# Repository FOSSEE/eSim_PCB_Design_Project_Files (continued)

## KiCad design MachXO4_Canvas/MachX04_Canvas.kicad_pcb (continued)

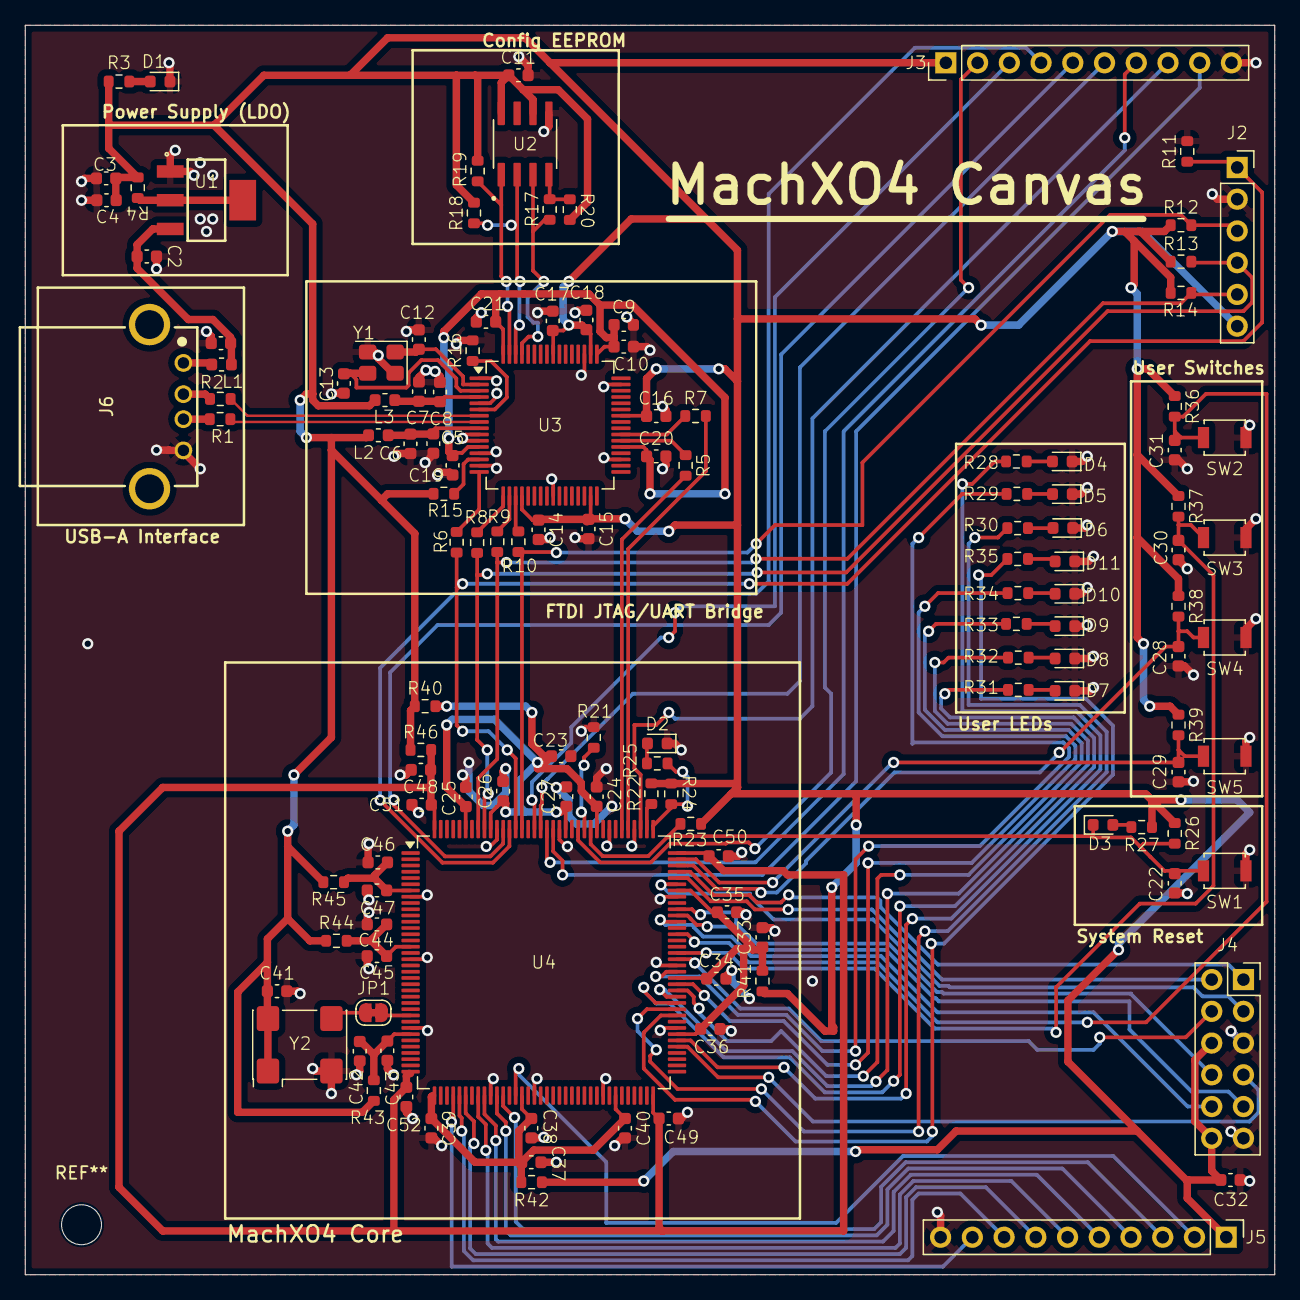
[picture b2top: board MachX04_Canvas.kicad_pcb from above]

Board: 2 copper layers, 100.0 x 100.0 mm, 129 parts (0 on the bottom side), 92 nets.

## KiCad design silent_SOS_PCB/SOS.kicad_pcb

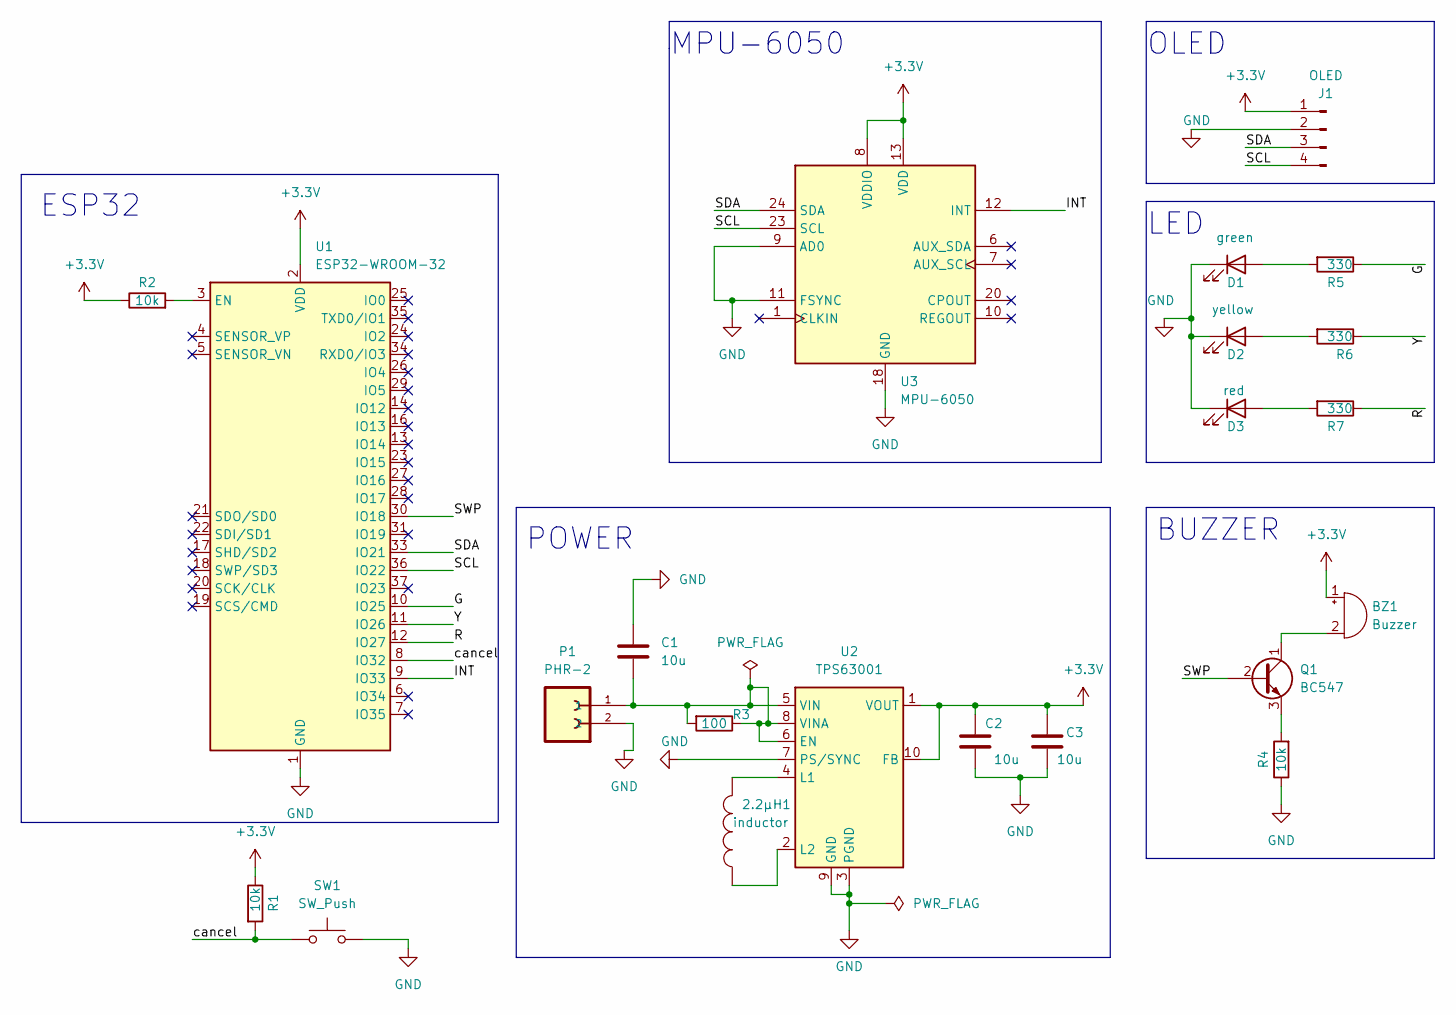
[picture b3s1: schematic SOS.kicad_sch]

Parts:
2.2µH1: inductor; L_0805_2012Metric
BZ1: Buzzer; Buzzer_CUI_CPT-9019S-SMT
C1, C2, C3: 10u; C_0805_2012Metric
D1: green; LED_0805_2012Metric
D2: yellow; LED_0805_2012Metric
D3: red; LED_0805_2012Metric
J1: OLED; PinHeader_1x04_P2.54mm_Vertical
P1: PHR-2; JST_PH_B2B-PH-K_1x02_P2.00mm_Vertical; MPN PHR-2
Q1: BC547; TO-92_Inline
R1, R2, R4: 10k; R_0805_2012Metric
R3: 100; R_0805_2012Metric
R5, R6, R7: 330; R_0805_2012Metric
SW1: SW_Push; SW_Push_SPST_NO_Alps_SKRK
U1: ESP32-WROOM-32
U2: TPS63001; Texas_DRC0010J_ThermalVias
U3: MPU-6050; InvenSense_QFN-24_4x4mm_P0.5mm

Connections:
+3.3V: BZ1.1 (-), C2.1, C3.1, J1.1, R1.1, R2.1, U1.2 (VDD), U2.1 (VOUT), U2.10 (FB), U3.8 (VDDIO), U3.13 (VDD)
/G: R5.1, U1.10 (IO25)
/INT: U1.9 (IO33), U3.12 (INT)
/R: R7.1, U1.12 (IO27)
/SCL: J1.4, U1.36 (IO22), U3.23 (SCL)
/SDA: J1.3, U1.33 (IO21), U3.24 (SDA)
/SWP: Q1.2 (B), U1.30 (IO18)
/Y: R6.1, U1.11 (IO26)
/cancel: R1.2, SW1.1, U1.8 (IO32)
GND: C1.1, C2.2, C3.2, D1.1 (K), D2.1 (K), D3.1 (K), J1.2, P1.2, R4.1, SW1.2, U1.1 (GND), U1.15 (GND), U1.38 (GND), U1.39 (GND), U2.3 (PGND), U2.7 (PS/SYNC), U2.9 (GND), U2.11 (PGND), U3.9 (AD0), U3.11 (FSYNC), U3.18 (GND)
unnamed: 2.2µH1.1, U2.2 (L2)
unnamed: 2.2µH1.2, U2.4 (L1)
unnamed: BZ1.2 (+), Q1.1 (C)
unnamed: C1.2, P1.1, R3.1, R3.2, U2.5 (VIN), U2.6 (EN), U2.8 (VINA)
unnamed: D1.2 (A), R5.2
unnamed: D2.2 (A), R6.2
unnamed: D3.2 (A), R7.2
unnamed: Q1.3 (E), R4.2
unnamed: R2.2, U1.3 (EN)

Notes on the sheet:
LED
POWER
BUZZER
ESP32
OLED
MPU-6050

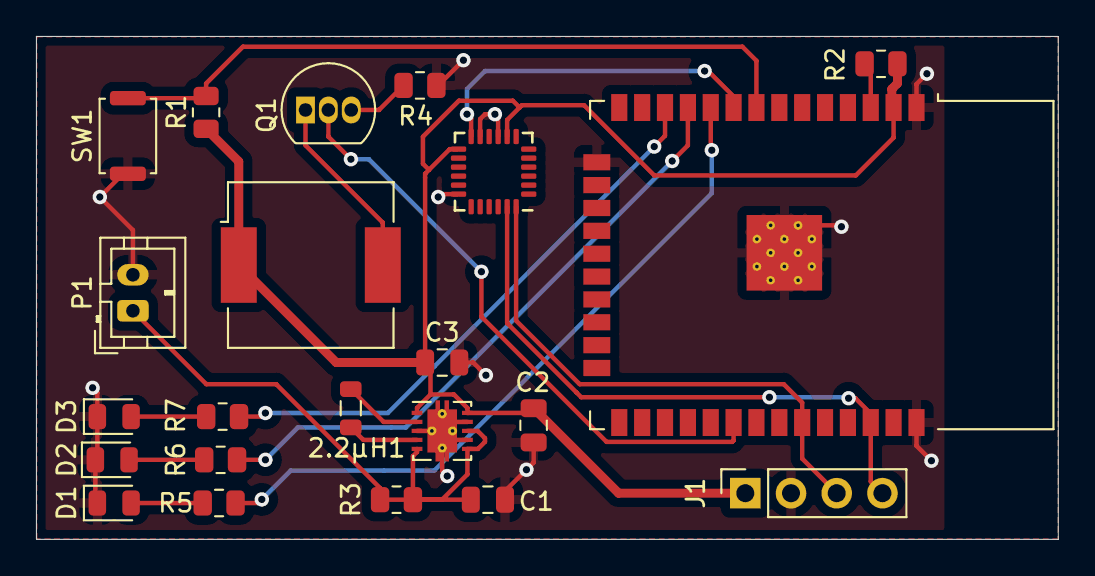
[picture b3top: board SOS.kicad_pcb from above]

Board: 2 copper layers, 56.8 x 27.9 mm, 22 parts (0 on the bottom side), 19 nets.

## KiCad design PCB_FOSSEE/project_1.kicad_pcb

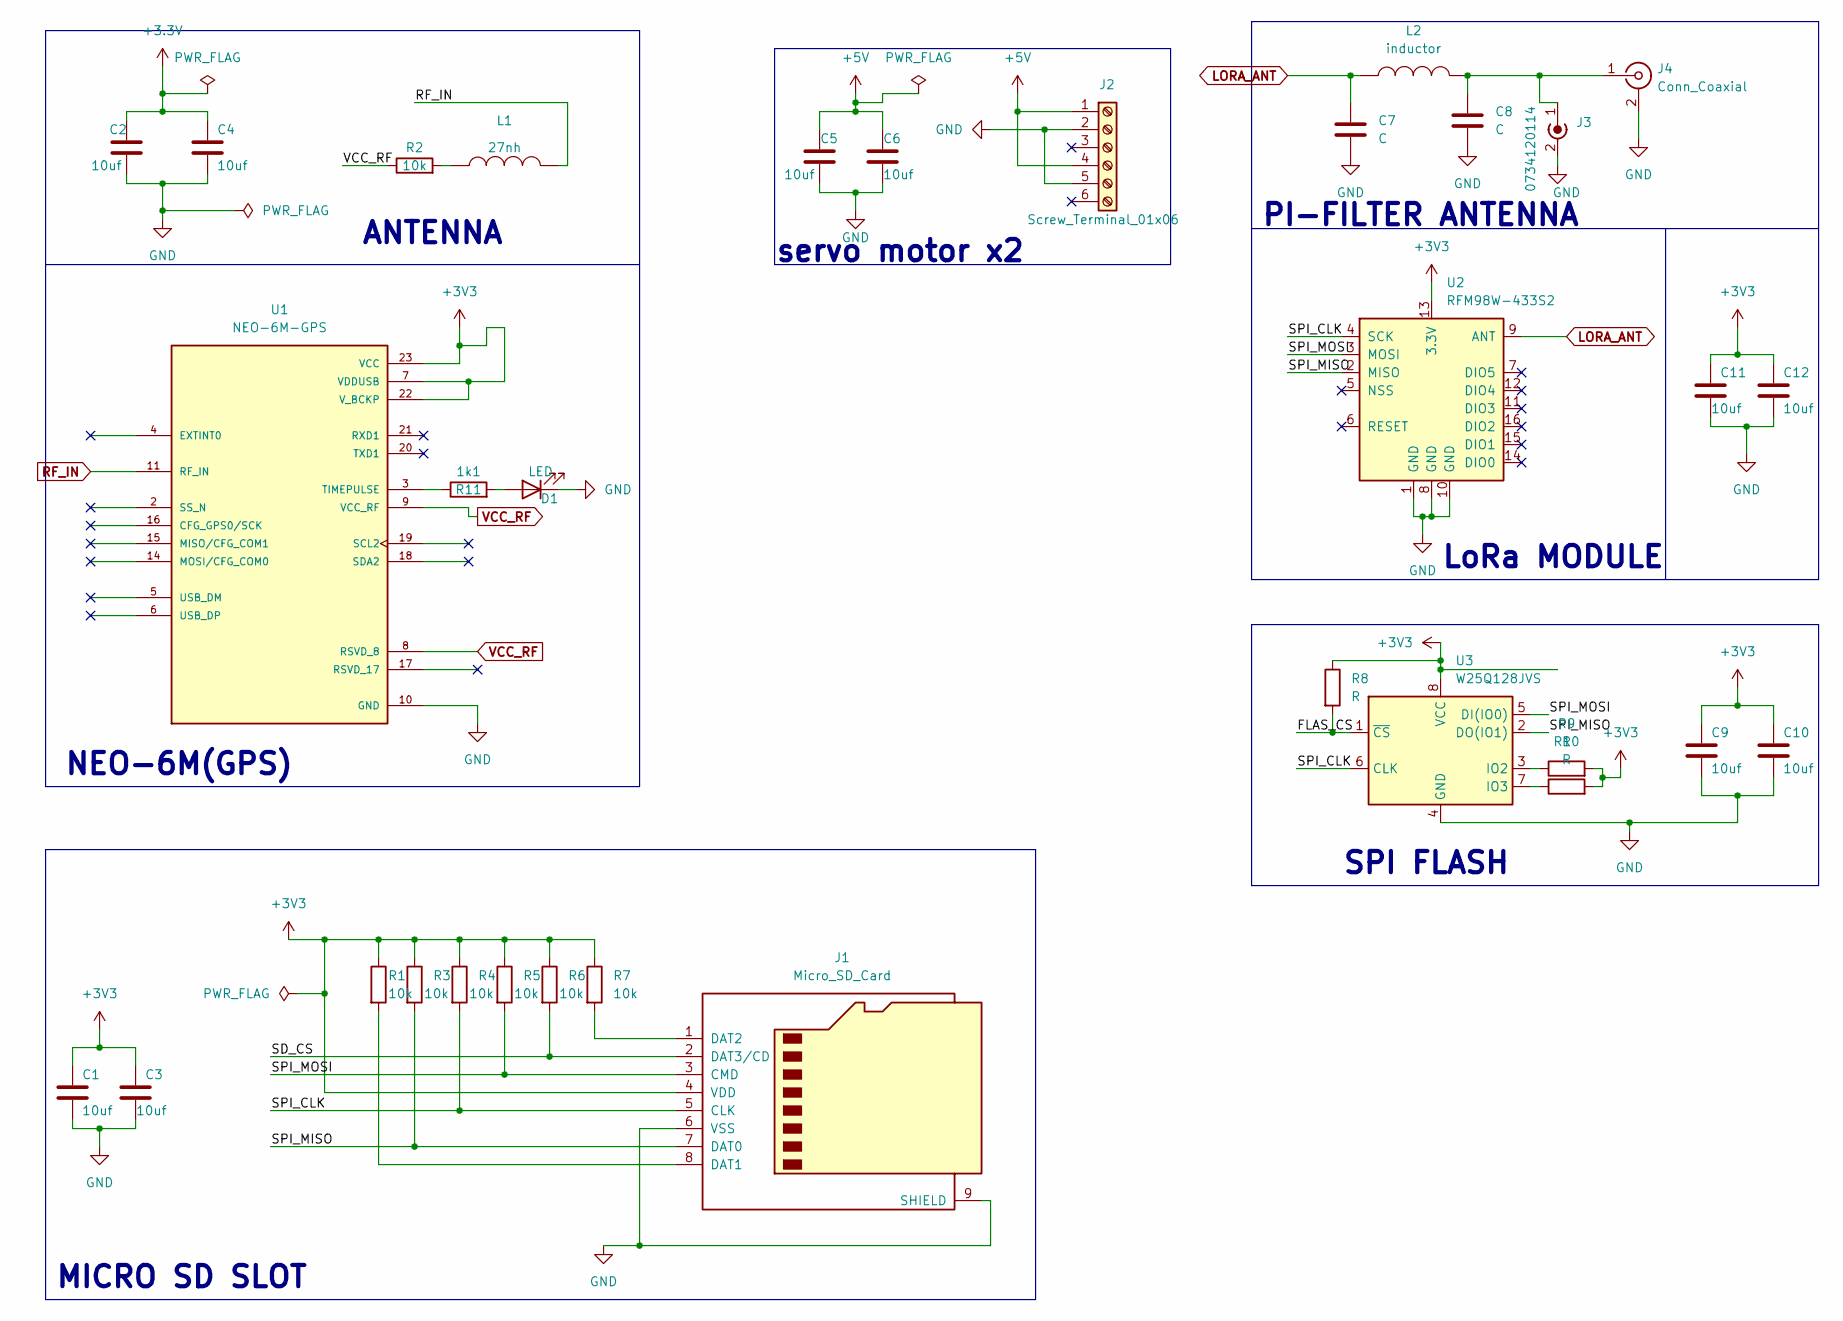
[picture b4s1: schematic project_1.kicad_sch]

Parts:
C1, C2, C3, C4, C5, C6, C9, C10, C11, C12: 10uf; C_0805_2012Metric
C7, C8: C; C_0805_2012Metric
D1: LED; LED_0805_2012Metric
J1: Micro_SD_Card; microSD_HC_Wuerth_693072010801
J2: Screw_Terminal_01x06; TerminalBlock_bornier-6_P5.08mm
J3: 0734120114; SMA_Molex_73251-1153_EdgeMount_Horizontal
J4: Conn_Coaxial; SMA_Molex_73251-2120_EdgeMount_Horizontal
L1: 27nh; L_0805_2012Metric
L2: inductor; L_0805_2012Metric
R1, R2, R3, R4, R5, R6, R7: 10k; R_0805_2012Metric
R8, R9, R10: R; R_0805_2012Metric
R11: 1k1; R_0805_2012Metric
U1: NEO-6M-GPS; ublox_NEO; MPN NEO-6M-GPS
U2: RFM98W-433S2; HOPERF_RFM9XW_SMD
U3: W25Q128JVS; SOIC-8_5.23x5.23mm_P1.27mm

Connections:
+3.3V: C2.1, C4.1
+3V3: C1.1, C3.1, C9.1, C10.1, C11.1, C12.1, J1.4 (VDD), R1.1, R3.1, R4.1, R5.1, R6.1, R7.1, R8.1, R9.2, R10.2, U1.7 (VDDUSB), U1.22 (V_BCKP), U1.23 (VCC), U2.13 (3.3V), U3.8 (VCC)
+5V: C5.1, C6.1, J2.1, J2.4
/FLAS_CS: R8.2, U3.1 (~CS)
/SD_CS: J1.2 (DAT3/CD), R6.2
/SPI_CLK: J1.5 (CLK), R4.2, U2.4 (SCK), U3.6 (CLK)
/SPI_MISO: J1.7 (DAT0), R3.2, U2.2 (MISO), U3.2 (DO(IO1))
/SPI_MOSI: J1.3 (CMD), R5.2, U2.3 (MOSI), U3.5 (DI(IO0))
GND: C1.2, C2.2, C3.2, C4.2, C5.2, C6.2, C7.2, C8.2, C9.2, C10.2, C11.2, C12.2, D1.1 (K), J1.6 (VSS), J1.9 (SHIELD), J2.2, J2.5, J3.2 (Ext), J4.2 (Ext), U1.10 (GND), U1.12 (GND), U1.13 (GND), U1.24 (GND), U2.1 (GND), U2.8 (GND), U2.10 (GND), U3.4 (GND)
LORA_ANT: C7.1, L2.1, U2.9 (ANT)
unnamed 10: R11.1, U1.3 (TIMEPULSE); also elsewhere on the board
unnamed 11: D1.2 (A), R11.2; also elsewhere on the board
unnamed: C8.1, J3.1 (In), J4.1 (In), L2.2
unnamed: J1.1 (DAT2), R7.2
unnamed: J1.8 (DAT1), R1.2
unnamed: L1.1, R2.2
unnamed: R9.1, U3.3 (IO2)
unnamed: R10.1, U3.7 (IO3)
RF_IN: L1.2, U1.11 (RF_IN)
VCC_RF: R2.1, U1.8 (RSVD_8), U1.9 (VCC_RF)

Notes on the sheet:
MICRO SD SLOT
SPI FLASH
ANTENNA
servo motor x2
LoRa MODULE
NEO-6M(GPS)
PI-FILTER ANTENNA

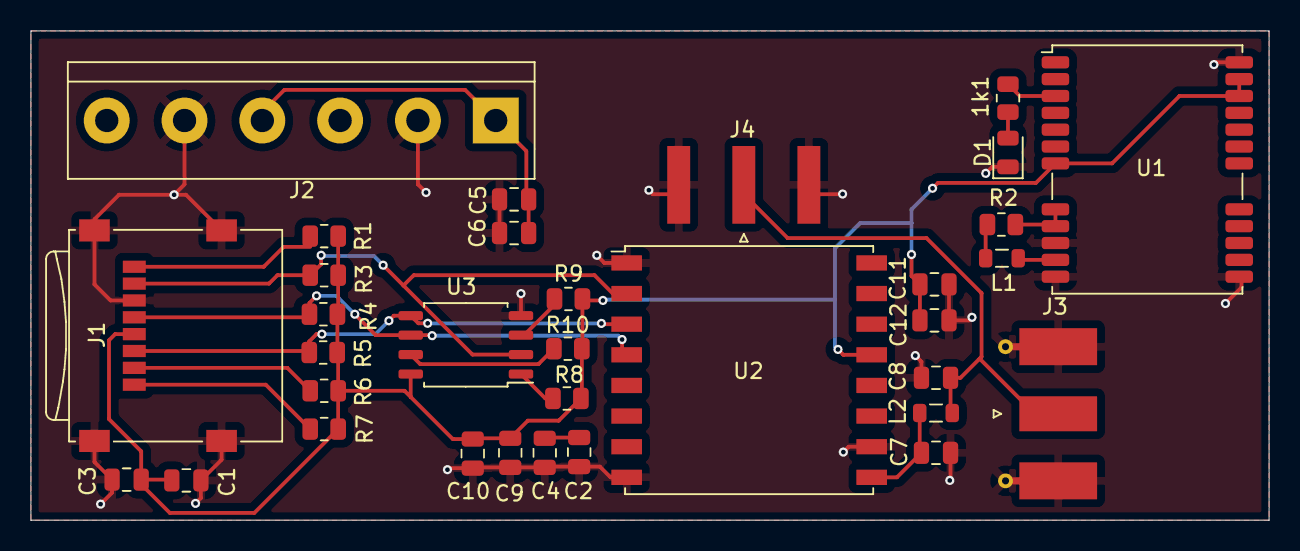
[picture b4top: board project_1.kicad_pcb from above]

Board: 2 copper layers, 80.8 x 32.0 mm, 33 parts (0 on the bottom side), 20 nets.

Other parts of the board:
1k1: R; R_0805_2012Metric

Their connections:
unnamed 10: 1k1.1; also elsewhere on the board
unnamed 11: 1k1.2; also elsewhere on the board

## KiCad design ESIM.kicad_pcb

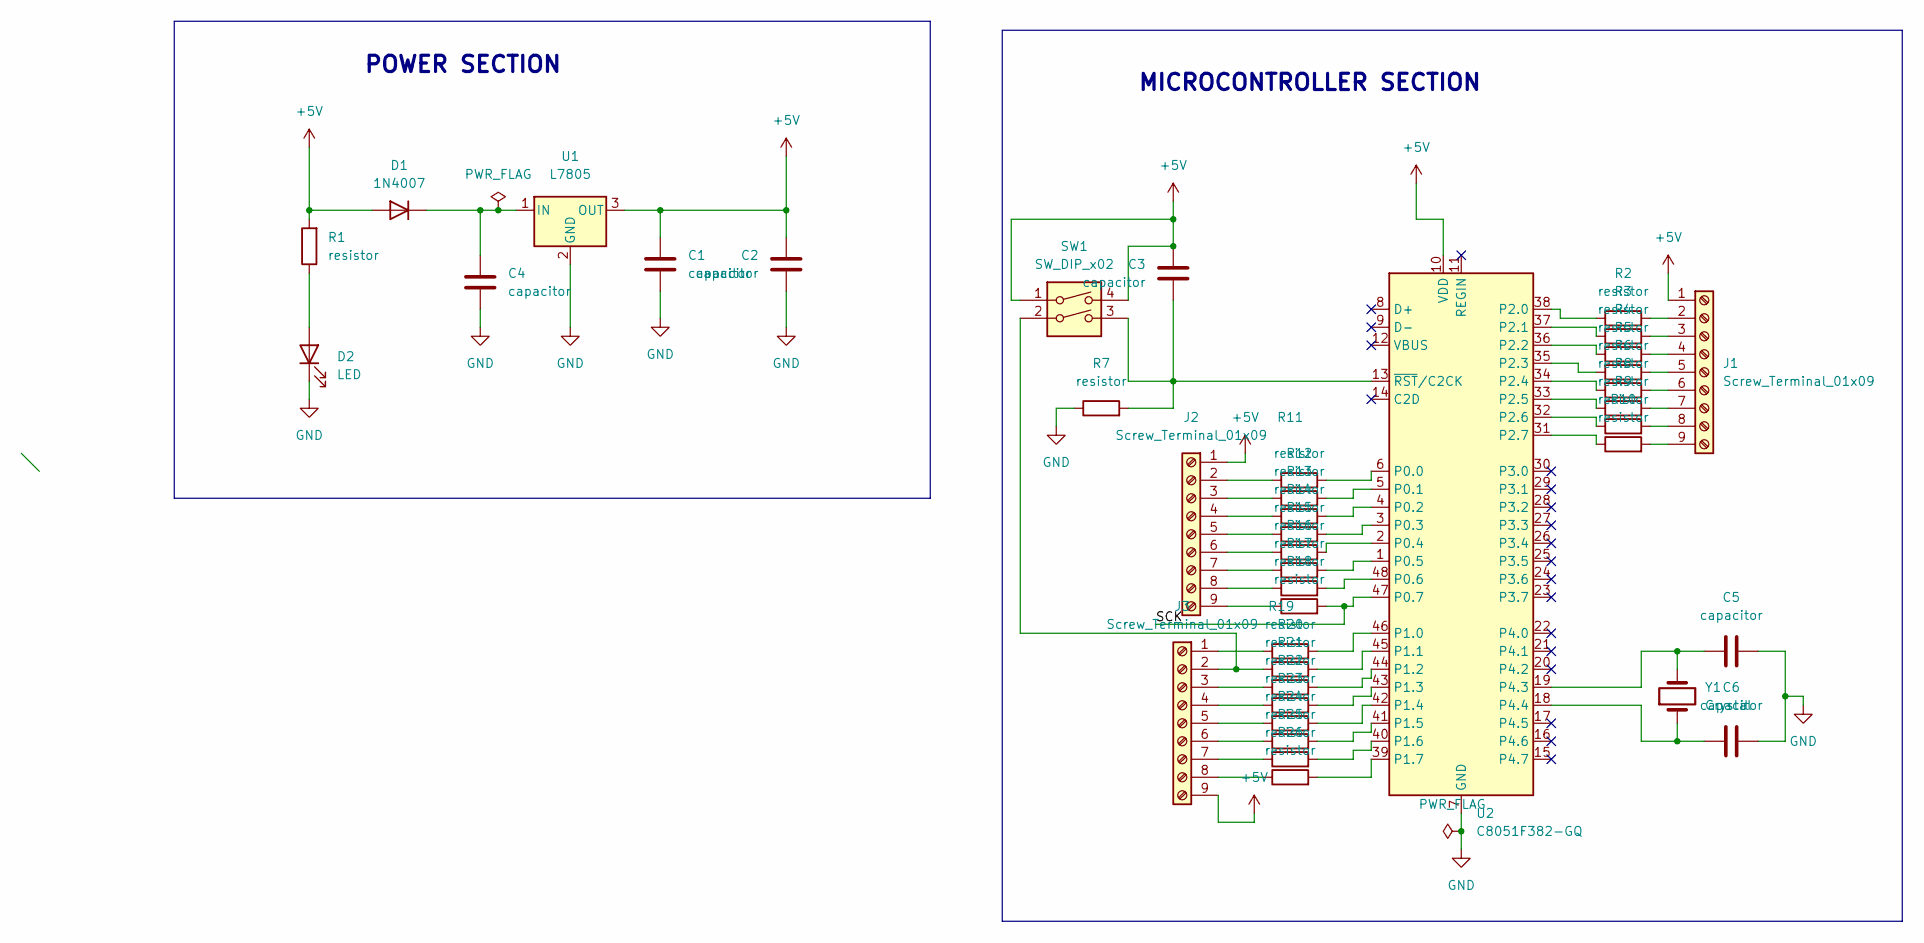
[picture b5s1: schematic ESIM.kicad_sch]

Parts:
C1, C2, C3, C4, C5, C6: capacitor; C_0603_1608Metric_Pad1.08x0.95mm_HandSolder
D1: 1N4007; D_DO-41_SOD81_P10.16mm_Horizontal
D2: LED; LED_0201_0603Metric
J1, J2, J3: Screw_Terminal_01x09; PinHeader_1x09_P1.00mm_Horizontal
R1, R2, R3, R4, R5, R6, R7, R8, R9, R10, R11, R12, R13, R14, R15, R16, R17, R18, R19, R20, R21, R22, R23, R24, R25, R26: resistor; R_0201_0603Metric
SW1: SW_DIP_x02; SW_DIP_SPSTx02_Slide_6.7x6.64mm_W6.73mm_P2.54mm_LowProfile_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
U1: L7805; TO-220-3_Vertical
U2: C8051F382-GQ; TQFP-48_7x7mm_P0.5mm
Y1: Crystal; Crystal_AT310_D3.0mm_L10.0mm_Horizontal

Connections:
+5V: C1.2, C2.2, C3.2, D1.2 (A), J1.1, J2.1, J3.9, R1.2, SW1.1, SW1.4, U1.3 (OUT), U2.10 (VDD)
/SCK: R18.2, U2.47 (P0.7)
GND: C1.1, C2.1, C4.1, C5.1, C6.1, D2.1 (K), R7.1, U1.2 (GND), U2.7 (GND)
unnamed: C3.1, R7.2, SW1.3, U2.13 (~RST/C2CK)
unnamed: C4.2, D1.1 (K), U1.1 (IN)
unnamed: C5.2, U2.19 (P4.3), Y1.2
unnamed: C6.2, U2.18 (P4.4), Y1.1
unnamed: D2.2 (A), R1.1
unnamed: J1.2, R2.2
unnamed: J1.3, R3.2
unnamed: J1.4, R4.2
unnamed: J1.5, R5.2
unnamed: J1.6, R6.2
unnamed: J1.7, R8.2
unnamed: J1.8, R9.2
unnamed: J1.9, R10.2
unnamed: J2.2, R11.1
unnamed: J2.3, R12.1
unnamed: J2.4, R13.1
unnamed: J2.5, R14.1
unnamed: J2.6, R15.1
unnamed: J2.7, R16.1
unnamed: J2.8, R17.1
unnamed: J2.9, R18.1
unnamed: J3.1, R19.1
unnamed: J3.2, R20.1, SW1.2
unnamed: J3.3, R21.1
unnamed: J3.4, R22.1
unnamed: J3.5, R23.1
unnamed: J3.6, R24.1
unnamed: J3.7, R25.1
unnamed: J3.8, R26.1
unnamed: R2.1, U2.38 (P2.0)
unnamed: R3.1, U2.37 (P2.1)
unnamed: R4.1, U2.36 (P2.2)
unnamed: R5.1, U2.35 (P2.3)
unnamed: R6.1, U2.34 (P2.4)
unnamed: R8.1, U2.33 (P2.5)
unnamed: R9.1, U2.32 (P2.6)
unnamed: R10.1, U2.31 (P2.7)
unnamed: R11.2, U2.6 (P0.0)
unnamed: R12.2, U2.5 (P0.1)
unnamed: R13.2, U2.4 (P0.2)
unnamed: R14.2, U2.3 (P0.3)
unnamed: R15.2, U2.2 (P0.4)
unnamed: R16.2, U2.1 (P0.5)
unnamed: R17.2, U2.48 (P0.6)
unnamed: R19.2, U2.46 (P1.0)
unnamed: R20.2, U2.45 (P1.1)
unnamed: R21.2, U2.44 (P1.2)
unnamed: R22.2, U2.43 (P1.3)
unnamed: R23.2, U2.42 (P1.4)
unnamed: R24.2, U2.41 (P1.5)
unnamed: R25.2, U2.40 (P1.6)
unnamed: R26.2, U2.39 (P1.7)

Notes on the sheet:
POWER SECTION
MICROCONTROLLER SECTION

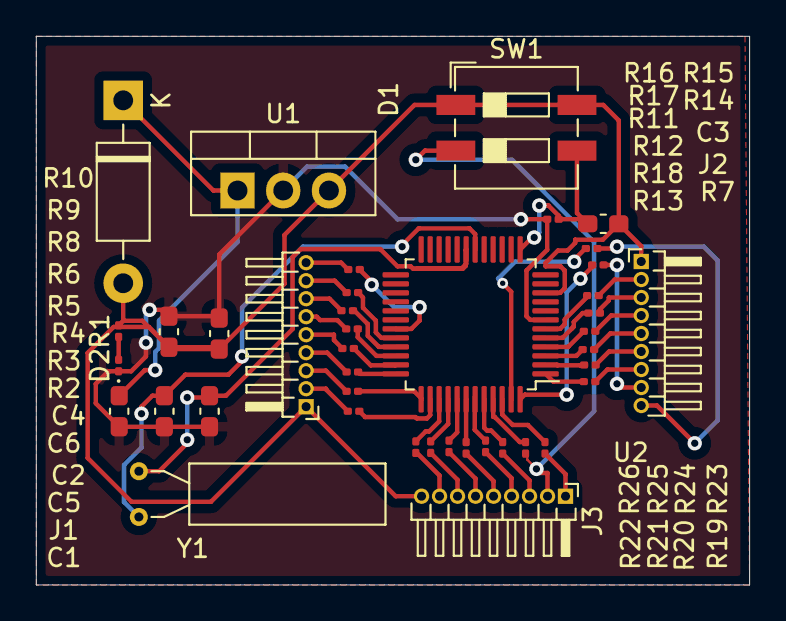
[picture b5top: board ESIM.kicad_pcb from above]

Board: 4 copper layers, 39.6 x 30.5 mm, 41 parts (0 on the bottom side), 55 nets.

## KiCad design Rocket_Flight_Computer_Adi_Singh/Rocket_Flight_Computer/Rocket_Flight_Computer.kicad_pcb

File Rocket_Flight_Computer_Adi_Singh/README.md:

# Rocket Flight Computer: eSim PCB Design (Task 7)

**eSim Semester Long Internship, Autumn 2026: Submission Task 7**
Adi Singh

This project was done for eSim 2.6.

A 2-layer ESP32 carrier board that serves as a flight computer for experimental model rockets. It provides IMUs, a barometer, micro-SD logging, LoRa/NRF24 telemetry, five servo outputs and a protected 5 V / 3.3 V power path.

## Quick facts

| | |
|---|---|
| Tool | eSim 2.6 (KiCad 10.0.7 back-end) |
| Board | 120 × 65 mm, 2 copper layers (F.Cu, B.Cu), GND pour on both layers |
| Parts | 48 footprints (ESP32 DevKit sockets, BNO085, MPU6050/MPU6500, BMP280, micro-SD, SX1278 LoRa / NRF24L01, 5 servo headers, LM1117-3.3 LDO) |
| Routing | 480 track segments, 70 vias (0.6/0.3 mm); 1.0 mm power, 0.5 mm 3V3, 0.25 mm signal |
| DRC | **0 violations, 0 unconnected pads, 0 schematic-parity issues** |
| ERC | **0 errors** (8 reviewed, intentional warnings; see report §7) |

## Repository layout

```
Rocket_Flight_Computer/            <- eSim project (open this folder in eSim)
  Rocket_Flight_Computer.proj        eSim project anchor
  Rocket_Flight_Computer.kicad_pro   KiCad project
  Rocket_Flight_Computer.kicad_sch   schematic
  Rocket_Flight_Computer.kicad_pcb   PCB layout
  Rocket_Flight_Computer.kicad_prl   project local settings
  sym-lib-table, fp-lib-table     project-local library tables (${KIPRJMOD})
  libs/                           custom symbols, footprints, 3D model
docs/
  Rocket_Flight_Computer_PCB_Report.pdf     full design report
  Rocket_Flight_Computer_PCB_Proposal.pdf   design proposal
  images/                                schematic, layout and 3D screenshots
outputs/
  schematic.pdf, BOM.csv, Rocket_Flight_Computer.net
  DRC.rpt, ERC.rpt
  Rocket_Flight_Computer_Gerbers.zip        Gerber + Excellon drill files
  pcb_*.svg                              layer plots
```

## Opening the project

1. In eSim: **Open Project** → select the `Rocket_Flight_Computer/` folder.
2. **Schematic Editor** opens `Rocket_Flight_Computer.kicad_sch`. **PCB Editor** opens the layout, where *Tools → Update PCB from Schematic* reports no changes.
3. *Inspect → Design Rules Checker* shows 0 errors. *View → 3D Viewer* shows the board render.

All non-standard symbols, footprints and the BNO085 3D model are bundled in `libs/` and referenced through project-local library tables, so the project opens without missing libraries.

## Design flow followed

Schematic in eSchema → footprint assignment → Update PCB from Schematic → manual 2-layer routing → DRC/ERC → 3D Viewer. Details, screenshots and design reasoning are in [the report](docs/Rocket_Flight_Computer_PCB_Report.pdf).

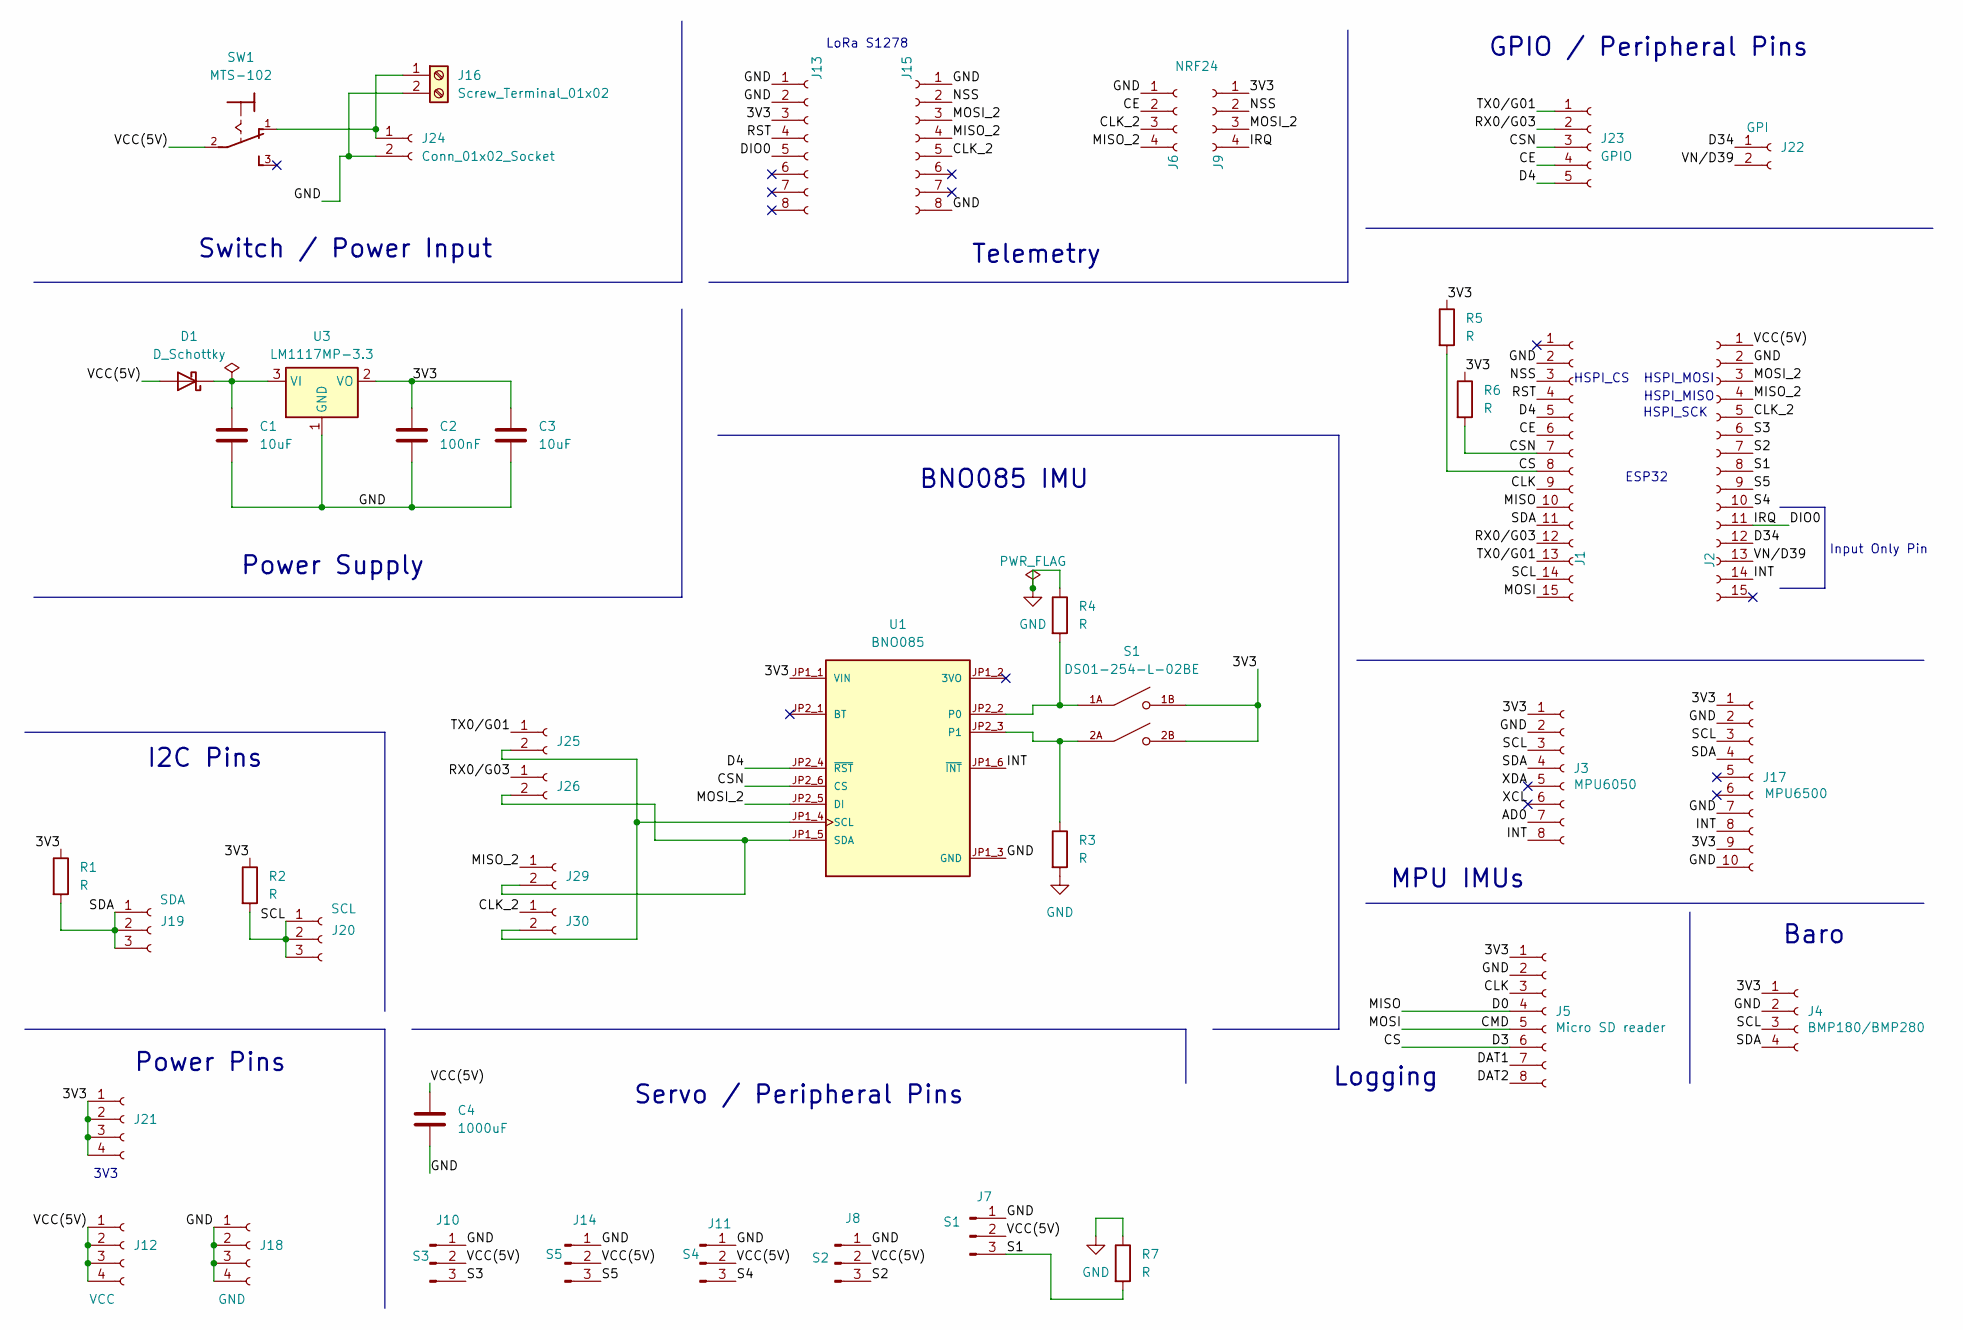
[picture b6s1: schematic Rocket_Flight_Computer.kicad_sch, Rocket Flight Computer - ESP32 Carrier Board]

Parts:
C1, C3: 10uF; C_Radial_D6.3mm_H11.0mm_P2.50mm
C2: 100nF; C_Disc_D5.0mm_W2.5mm_P5.00mm
C4: 1000uF; C_Radial_D8.0mm_H7.0mm_P3.50mm
D1: D_Schottky; D_DO-41_SOD81_P7.62mm_Horizontal
J1, J2: Conn_01x15_Socket; PinSocket_1x15_P2.54mm_Vertical
J3, J5: Conn_01x08_Socket; PinSocket_1x08_P2.54mm_Vertical
J4, J6, J9, J12, J18, J21: Conn_01x04_Socket; PinSocket_1x04_P2.54mm_Vertical
J7, J8, J10, J11, J14: Conn_01x03_Pin; PinSocket_1x03_P2.54mm_Vertical
J13, J15: Conn_01x08_Socket; PinHeader_1x08_P2.54mm_Vertical
J16: Screw_Terminal_01x02; TerminalBlock_MaiXu_MX126-5.0-02P_1x02_P5.00mm
J17: Conn_01x10_Socket; PinSocket_1x10_P2.54mm_Vertical
J19, J20: Conn_01x03_Socket; PinSocket_1x03_P2.54mm_Vertical
J22: GPI; PinHeader_1x02_P2.54mm_Vertical
J23: GPIO; PinHeader_1x05_P2.54mm_Vertical
J24: Conn_01x02_Socket; PinSocket_1x02_P2.54mm_Vertical
J25, J26, J29, J30: Conn_01x02_Socket; PinHeader_1x02_P2.54mm_Vertical
R1, R2, R3, R4, R5, R6, R7: R; R_Axial_DIN0207_L6.3mm_D2.5mm_P7.62mm_Horizontal
S1: DS01-254-L-02BE; SW_DS01-254-L-02BE; PARTREV 1.0
SW1: MTS-102
U1: BNO085; MODULE_4754; PARTREV 2021-03-16
U3: LM1117MP-3.3; SOT-223-3_TabPin2

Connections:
/3V3: C2.1, C3.1, J3.1, J4.1, J5.1, J9.1, J13.3, J17.1, J17.9, J21.1, J21.2, J21.3, J21.4, R1.1, R2.1, R5.1, R6.1, S1.1B, S1.2B, U1.JP1_1 (VIN), U3.2 (VO)
/AD0: J3.7
/CE: J1.6, J6.2, J23.4
/CLK: J1.9, J5.3
/CLK_2: J2.5, J6.3, J15.5, J30.1
/CMD: J1.15, J5.5
/CS: J1.8, J5.6, R5.2
/CSN: J1.7, J23.3, R6.2, U1.JP2_6 (CS)
/D0: J1.10, J5.4
/D4: J1.5, J23.5, U1.JP2_4 (~RST)
/D34: J2.12, J22.1
/DAT1: J5.7
/DAT2: J5.8
/DIO0: J2.11, J9.4, J13.5
/INT: J2.14, J3.8, J17.8, U1.JP1_6 (~INT)
/MISO_2: J2.4, J6.4, J15.4, J29.1
/MOSI_2: J2.3, J9.3, J15.3, U1.JP2_5 (DI)
/NSS: J1.3, J9.2, J15.2
/RST: J1.4, J13.4
/RX0/G03: J1.12, J23.2, J26.1
/S1: J2.8, J7.3, R7.2
/S2: J2.7, J8.3
/S3: J2.6, J10.3
/S4: J2.10, J11.3
/S5: J2.9, J14.3
/SCL: J1.14, J3.3, J4.3, J17.3, J20.1, J20.2, J20.3, R2.2
/SDA: J1.11, J3.4, J4.4, J17.4, J19.1, J19.2, J19.3, R1.2
/TX0/G01: J1.13, J23.1, J25.1
/VCC(5V): C4.1, D1.2 (A), J2.1, J7.2, J8.2, J10.2, J11.2, J12.1, J12.2, J12.3, J12.4, J14.2, SW1.2
/VN/D39: J2.13, J22.2
/XCL: J3.6
/XDA: J3.5
GND: C1.2, C2.2, C3.2, C4.2, J1.2, J2.2, J3.2, J4.2, J5.2, J6.1, J7.1, J8.1, J10.1, J11.1, J13.1, J13.2, J14.1, J15.1, J15.8, J16.2, J17.2, J17.7, J17.10, J18.1, J18.2, J18.3, J18.4, J24.2, R3.2, R4.1, R7.1, U1.JP1_3 (GND), U3.1 (GND); also elsewhere on the board
unnamed: C1.1, D1.1 (K), U3.3 (VI)
unnamed: J16.1, J24.1, SW1.1
unnamed: J25.2, J30.2, U1.JP1_4 (SCL)
unnamed: J26.2, J29.2, U1.JP1_5 (SDA)
unnamed: R4.2, S1.1A, U1.JP2_2 (P0)
unnamed: R3.1, S1.2A, U1.JP2_3 (P1)

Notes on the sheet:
GPIO / Peripheral Pins
Telemetry
Logging
Servo / Peripheral Pins
ESP32
LoRa S1278
I2C Pins
Baro
3V3
HSPI_SCK
HSPI_MOSI
HSPI_CS
MPU IMUs
Power Pins
HSPI_MISO
Power Supply
Input Only Pin
BNO085 IMU
Switch / Power Input

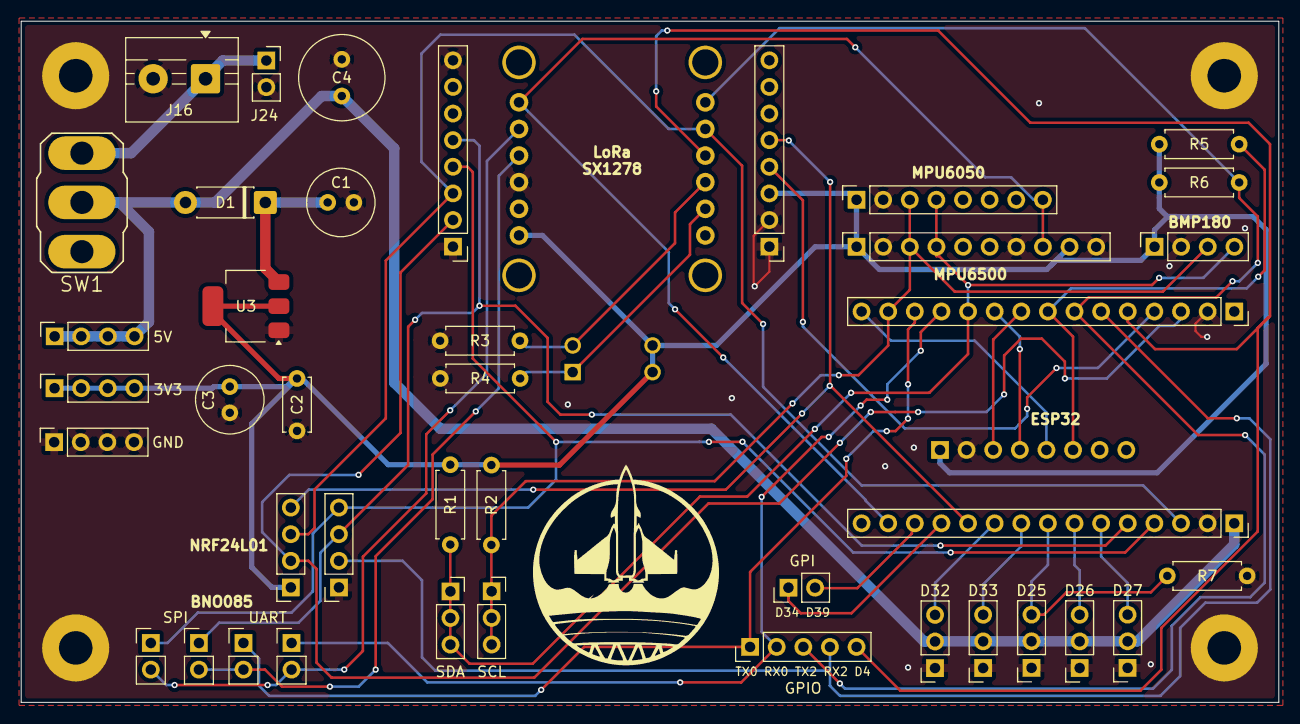
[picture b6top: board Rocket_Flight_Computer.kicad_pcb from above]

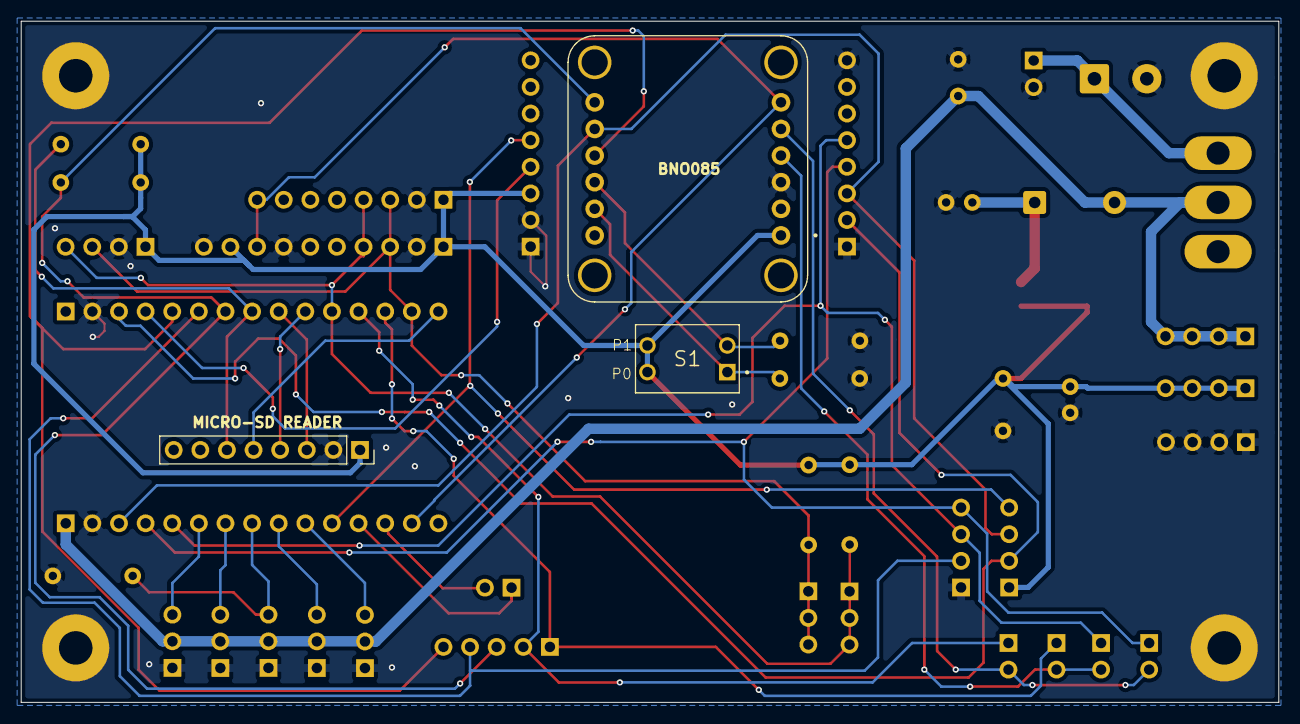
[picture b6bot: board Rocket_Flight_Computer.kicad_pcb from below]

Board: 2 copper layers, 120.0 x 65.0 mm, 48 parts (3 on the bottom side), 34 nets.

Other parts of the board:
H1, H2, H3, H4: MountingHole_3.2mm_M3_Pad

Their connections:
GND: H1.1, H2.1, H3.1, H4.1; also elsewhere on the board

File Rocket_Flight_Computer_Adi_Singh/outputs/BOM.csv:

"Reference","Value","Footprint","Qty"
"C1,C3","10uF","Capacitor_THT:C_Radial_D6.3mm_H11.0mm_P2.50mm","2"
"C2","100nF","Capacitor_THT:C_Disc_D5.0mm_W2.5mm_P5.00mm","1"
"C4","1000uF","Capacitor_THT:C_Radial_D8.0mm_H7.0mm_P3.50mm","1"
"D1","D_Schottky","Diode_THT:D_DO-41_SOD81_P7.62mm_Horizontal","1"
"J1,J2","Conn_01x15_Socket","Connector_PinSocket_2.54mm:PinSocket_1x15_P2.54mm_Vertical","2"
"J3,J5","Conn_01x08_Socket","Connector_PinSocket_2.54mm:PinSocket_1x08_P2.54mm_Vertical","2"
"J4,J6,J9,J12,J18,J21","Conn_01x04_Socket","Connector_PinSocket_2.54mm:PinSocket_1x04_P2.54mm_Vertical","6"
"J7,J8,J10,J11,J14","Conn_01x03_Pin","Connector_PinSocket_2.54mm:PinSocket_1x03_P2.54mm_Vertical","5"
"J13,J15","Conn_01x08_Socket","Connector_PinHeader_2.54mm:PinHeader_1x08_P2.54mm_Vertical","2"
"J16","Screw_Terminal_01x02","TerminalBlock:TerminalBlock_MaiXu_MX126-5.0-02P_1x02_P5.00mm","1"
"J17","Conn_01x10_Socket","Connector_PinSocket_2.54mm:PinSocket_1x10_P2.54mm_Vertical","1"
"J19,J20","Conn_01x03_Socket","Connector_PinSocket_2.54mm:PinSocket_1x03_P2.54mm_Vertical","2"
"J22","GPI","Connector_PinHeader_2.54mm:PinHeader_1x02_P2.54mm_Vertical","1"
"J23","GPIO","Connector_PinHeader_2.54mm:PinHeader_1x05_P2.54mm_Vertical","1"
"J24","Conn_01x02_Socket","Connector_PinSocket_2.54mm:PinSocket_1x02_P2.54mm_Vertical","1"
"J25,J26,J29,J30","Conn_01x02_Socket","Connector_PinHeader_2.54mm:PinHeader_1x02_P2.54mm_Vertical","4"
"R1,R2,R3,R4,R5,R6,R7","R","Resistor_THT:R_Axial_DIN0207_L6.3mm_D2.5mm_P7.62mm_Horizontal","7"
"S1","DS01-254-L-02BE","two-way-slide-switch:SW_DS01-254-L-02BE","1"
"SW1","MTS-102","MTS-102:MTS-102","1"
"U1","BNO085","Adafruit-BNO085:MODULE_4754","1"
"U3","LM1117MP-3.3","Package_TO_SOT_SMD:SOT-223-3_TabPin2","1"
